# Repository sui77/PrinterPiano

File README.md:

# PrinterPiano
This tiny keyboard will turn your 3d printer itself into a music instrument. 

@see https://www.printables.com/model/444297

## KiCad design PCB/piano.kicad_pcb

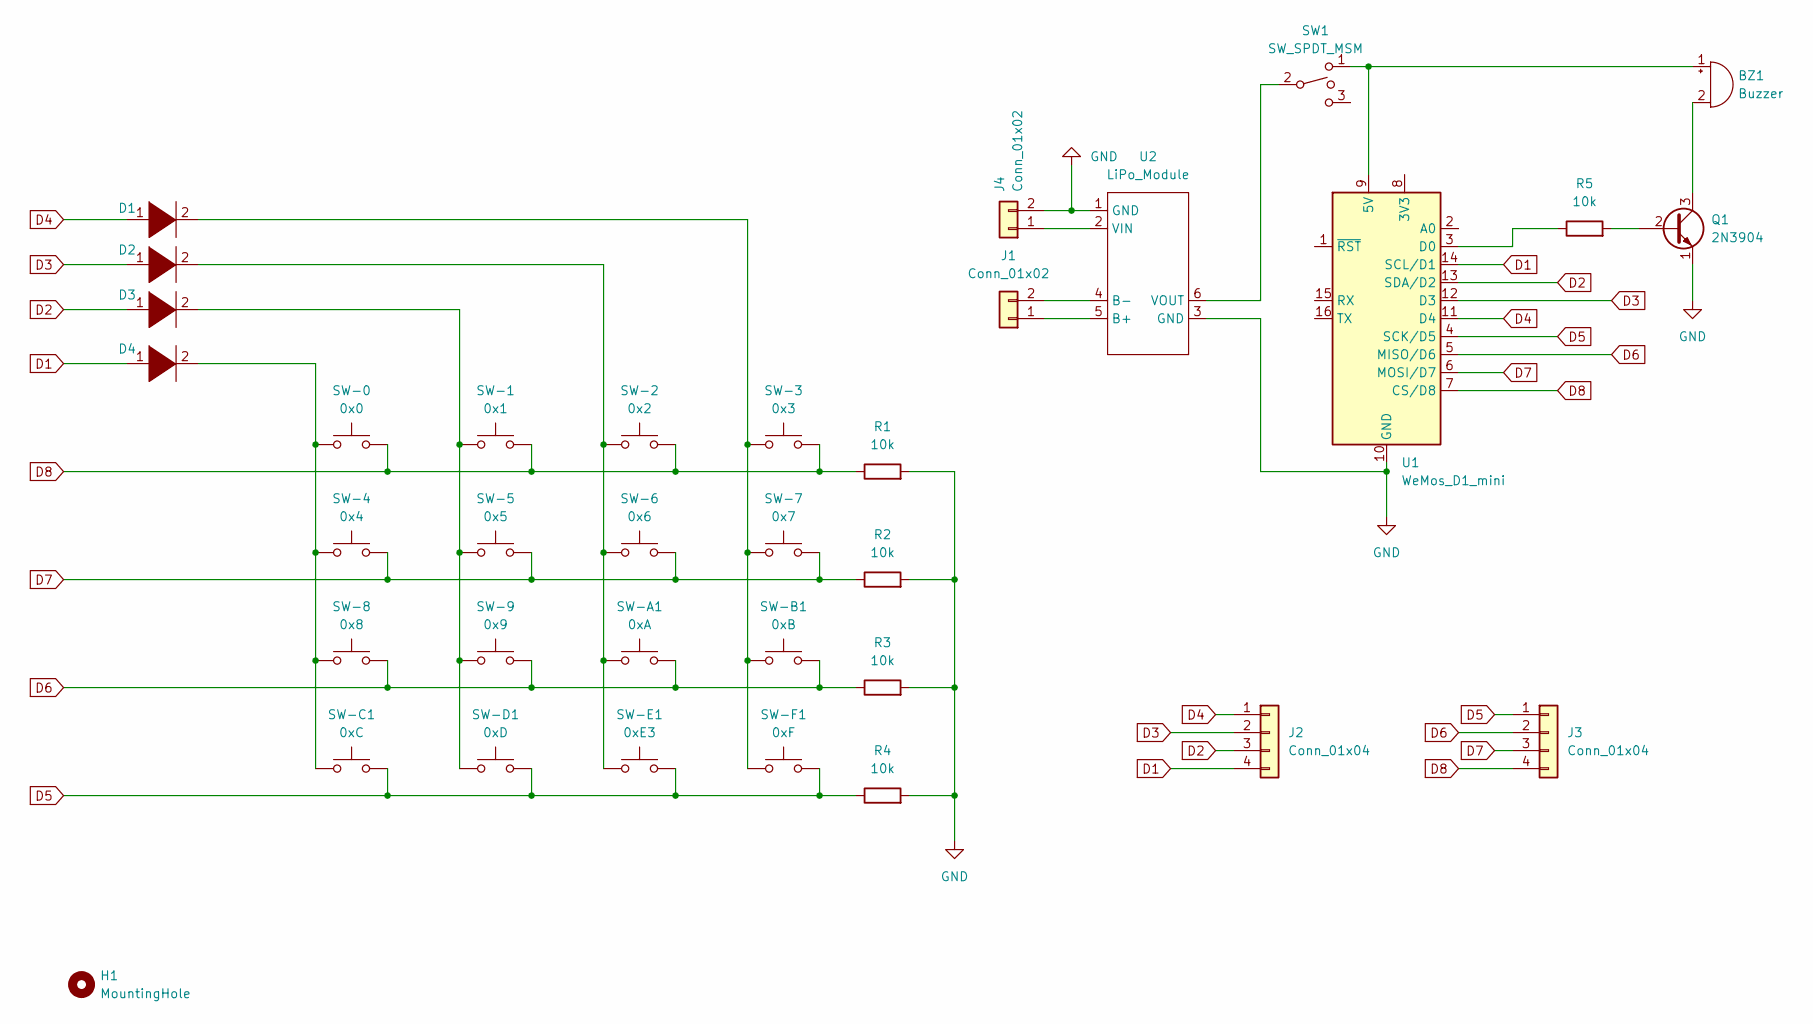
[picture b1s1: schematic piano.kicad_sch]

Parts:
BZ1: Buzzer; Buzzer_12x9.5RM7.6
D1, D2, D3, D4: DIODE; D_0805_2012Metric
H1: MountingHole
J1, J4: Conn_01x02; JST_EH_B2B-EH-A_1x02_P2.50mm_Vertical
J2, J3: Conn_01x04; PinHeader_1x04_P2.54mm_Vertical
Q1: 2N3904; TO-92_Inline
R1, R2, R3, R4, R5: 10k; R_1206_3216Metric_Pad1.30x1.75mm_HandSolder
SW1: SW_SPDT_MSM; Schiebeschalter
SW-0: 0x0; SW_PUSH_6mm
SW-1: 0x1; SW_PUSH_6mm
SW-2: 0x2; SW_PUSH_6mm
SW-3: 0x3; SW_PUSH_6mm
SW-4: 0x4; SW_PUSH_6mm
SW-5: 0x5; SW_PUSH_6mm
SW-6: 0x6; SW_PUSH_6mm
SW-7: 0x7; SW_PUSH_6mm
SW-8: 0x8; SW_PUSH_6mm
SW-9: 0x9; SW_PUSH_6mm
SW-A1: 0xA; SW_PUSH_6mm
SW-B1: 0xB; SW_PUSH_6mm
SW-C1: 0xC; SW_PUSH_6mm
SW-D1: 0xD; SW_PUSH_6mm
SW-E1: 0xE3; SW_PUSH_6mm
SW-F1: 0xF; SW_PUSH_6mm
U1: WeMos_D1_mini; WEMOS_D1_mini_light
U2: LiPo_Module; LiPoChargerModule

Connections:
D1: D4.1 (K), J2.4, U1.14 (SCL/D1)
D2: D3.1 (K), J2.3, U1.13 (SDA/D2)
D3: D2.1 (K), J2.2, U1.12 (D3)
D4: D1.1 (K), J2.1, U1.11 (D4)
D5: J3.1, R4.1, SW-C1.2, SW-D1.2, SW-E1.2, SW-F1.2, U1.4 (SCK/D5)
D6: J3.2, R3.1, SW-8.2, SW-9.2, SW-A1.2, SW-B1.2, U1.5 (MISO/D6)
D7: J3.3, R2.1, SW-4.2, SW-5.2, SW-6.2, SW-7.2, U1.6 (MOSI/D7)
D8: J3.4, R1.1, SW-0.2, SW-1.2, SW-2.2, SW-3.2, U1.7 (CS/D8)
GND: J4.2, Q1.1 (E), R1.2, R2.2, R3.2, R4.2, U1.10 (GND), U2.1 (GND), U2.3 (GND)
unnamed: BZ1.2 (+), Q1.3 (C)
unnamed: D1.2 (A), SW-3.1, SW-7.1, SW-B1.1, SW-F1.1
unnamed: D2.2 (A), SW-2.1, SW-6.1, SW-A1.1, SW-E1.1
unnamed: D3.2 (A), SW-1.1, SW-5.1, SW-9.1, SW-D1.1
unnamed: D4.2 (A), SW-0.1, SW-4.1, SW-8.1, SW-C1.1
unnamed: J1.1, U2.5 (B+)
unnamed: J1.2, U2.4 (B-)
unnamed: J4.1, U2.2 (VIN)
unnamed: Q1.2 (B), R5.2
unnamed: BZ1.1 (-), SW1.1, U1.9 (5V)
unnamed: SW1.2, U2.6 (VOUT)
unnamed: R5.1, U1.3 (D0)

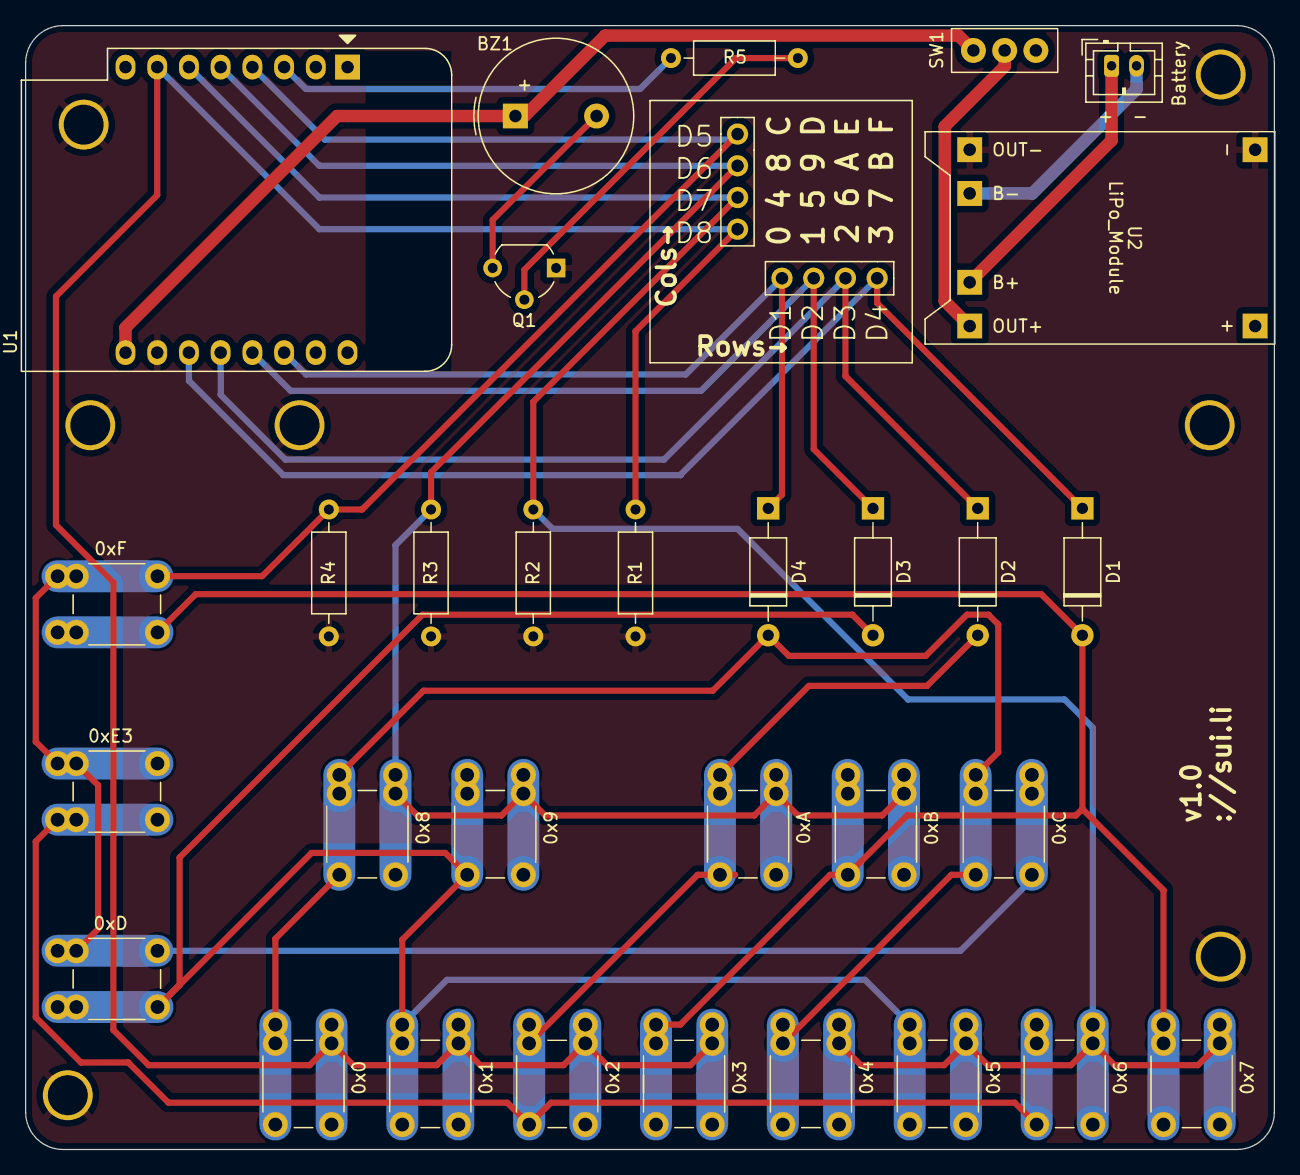
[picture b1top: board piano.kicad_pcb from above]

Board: 2 copper layers, 100.0 x 90.0 mm, 33 parts (0 on the bottom side), 20 nets.

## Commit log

2023-04-07 initial load
2023-04-07 support for http/https
2023-04-25 v0.2 PCB
2023-05-05 update pcb (larger footprint for transistor)
2023-05-05 update case model
